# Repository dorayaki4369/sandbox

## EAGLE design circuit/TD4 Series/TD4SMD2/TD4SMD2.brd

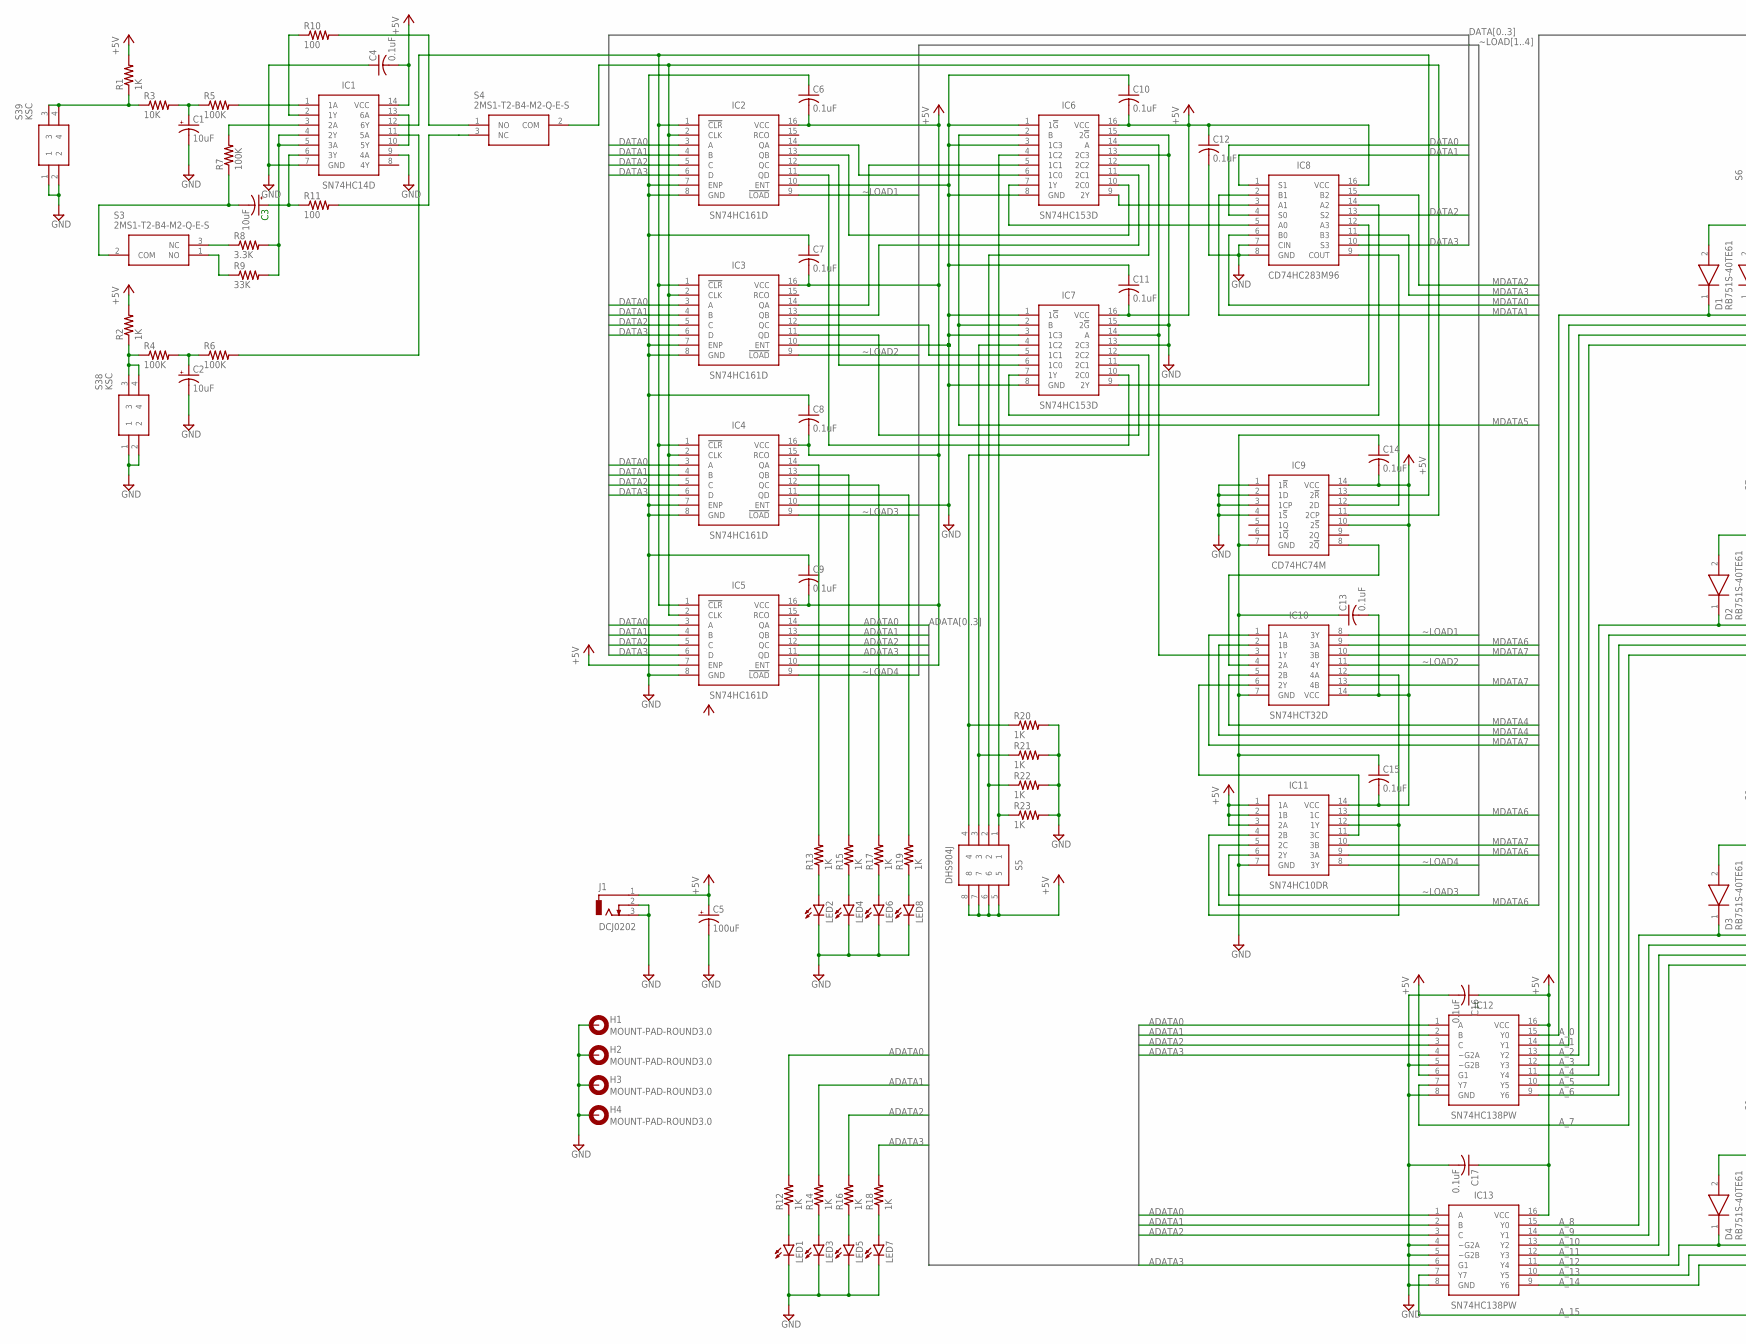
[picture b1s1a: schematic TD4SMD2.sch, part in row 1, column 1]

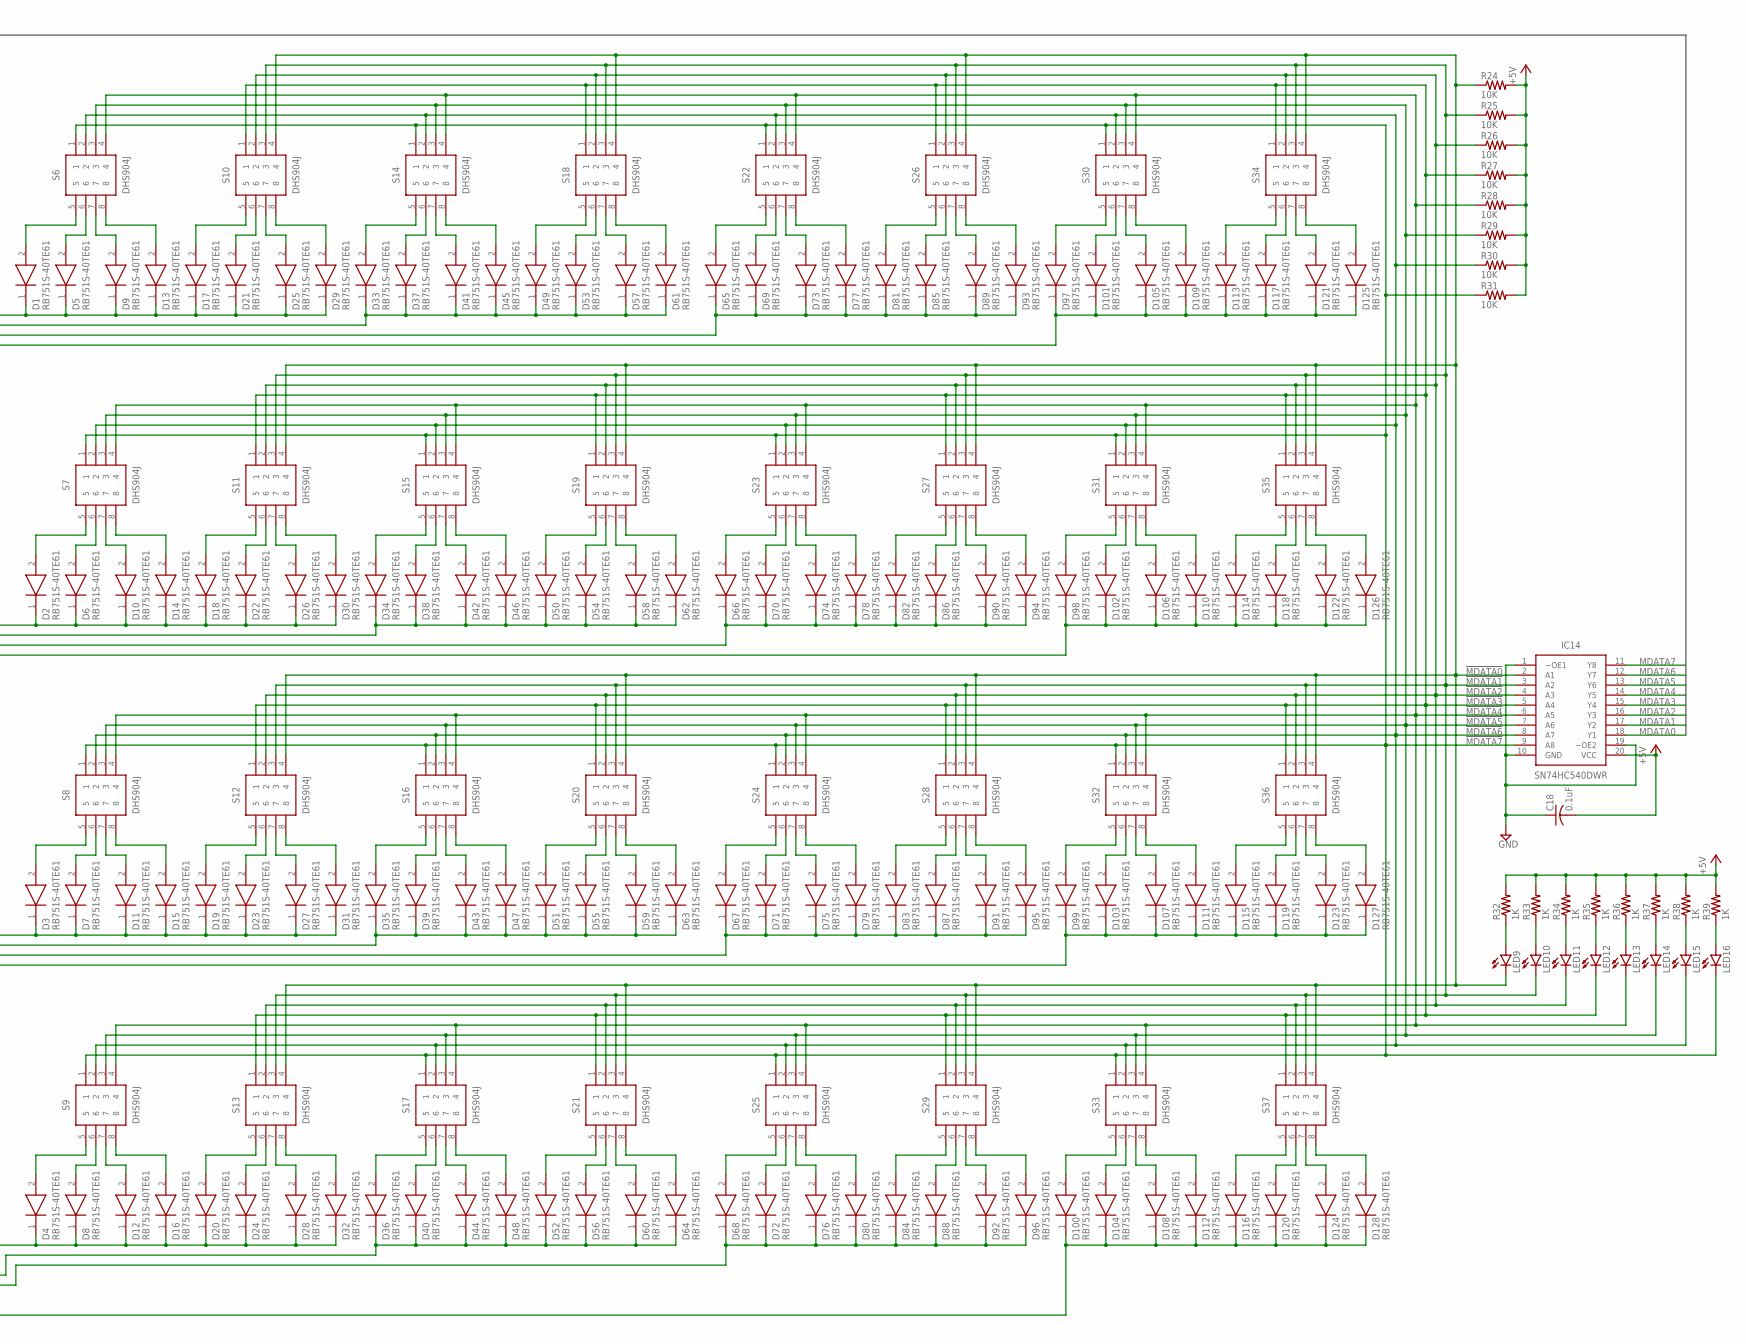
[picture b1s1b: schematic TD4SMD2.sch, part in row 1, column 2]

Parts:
C1, C2, C3: 10uF; 153CLV-0405
C4, C6, C7, C8, C9, C10, C11, C12, C13, C14, C15, C16, C17, C18: 0.1uF; C0603
C5: 100uF; 153CLV-1010
D1, D2, D3, D4, D5, D6, D7, D8, D9, D10, D11, D12, D13, D14, D15, D16, D17, D18, D19, D20, D21, D22, D23, D24, D25, D26, D27, D28, D29, D30, D31, D32, D33, D34, D35, D36, D37, D38, D39, D40, D41, D42, D43, D44, D45, D46, D47, D48, D49, D50, D51, D52, D53, D54, D55, D56, D57, D58, D59, D60, D61, D62, D63, D64, D65, D66, D67, D68, D69, D70, D71, D72, D73, D74, D75, D76, D77, D78, D79, D80, D81, D82, D83, D84, D85, D86, D87, D88, D89, D90, D91, D92, D93, D94, D95, D96, D97, D98, D99, D100, D101, D102, D103, D104, D105, D106, D107, D108, D109, D110, D111, D112, D113, D114, D115, D116, D117, D118, D119, D120, D121, D122, D123, D124, D125, D126, D127, D128: RB751S-40TE61; SODFL1608X70N
H1, H2, H3, H4: MOUNT-PAD-ROUND3.0; 3,0-PAD
IC1: SN74HC14D; SOIC127P600X175-14N
IC2, IC3, IC4, IC5: SN74HC161D; SOIC127P600X175-16N
IC6, IC7: SN74HC153D; SOIC127P600X175-16N
IC8: CD74HC283M96; SOIC127P600X175-16N
IC9: CD74HC74M; SOIC127P600X175-14N
IC10: SN74HCT32D; SOIC127P600X175-14N
IC11: SN74HC10DR; SOIC127P600X175-14N
IC12, IC13: SN74HC138PW; SOP65P640X120-16N
IC14: SN74HC540DWR; SOIC127P1030X265-20N
J1: DCJ0202
LED1, LED2, LED3, LED4, LED5, LED6, LED7, LED8, LED9, LED10, LED11, LED12, LED13, LED14, LED15, LED16: LEDCHIP-LED0603; CHIP-LED0603
R1, R2, R12, R13, R14, R15, R16, R17, R18, R19, R20, R21, R22, R23, R32, R33, R34, R35, R36, R37, R38, R39: 1K; R0603
R3, R24, R25, R26, R27, R28, R29, R30, R31: 10K; R0603
R4, R5, R6, R7: 100K; R0603
R8: 3.3K; R0603
R9: 33K; R0603
R10, R11: 100; R0603
S3, S4: 2MS1-T2-B4-M2-Q-E-S; 2MS1T2B4M2QES
S5, S6, S7, S8, S9, S10, S11, S12, S13, S14, S15, S16, S17, S18, S19, S20, S21, S22, S23, S24, S25, S26, S27, S28, S29, S30, S31, S32, S33, S34, S35, S36, S37: DHS904J
S38, S39: KSC

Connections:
!MDATA0: IC14.2 (A1), LED9.C, R24.1, S10.4, S11.4, S12.4, S13.4, S18.4, S19.4, S20.4, S21.4, S26.4, S27.4, S28.4, S29.4, S34.4, S35.4, S36.4, S37.4
!MDATA1: IC14.3 (A2), LED10.C, R25.1, S10.3, S11.3, S12.3, S13.3, S18.3, S19.3, S20.3, S21.3, S26.3, S27.3, S28.3, S29.3, S34.3, S35.3, S36.3, S37.3
!MDATA2: IC14.4 (A3), LED11.C, R26.1, S10.2, S11.2, S12.2, S13.2, S18.2, S19.2, S20.2, S21.2, S26.2, S27.2, S28.2, S29.2, S34.2, S35.2, S36.2, S37.2
!MDATA3: IC14.5 (A4), LED12.C, R27.1, S10.1, S11.1, S12.1, S13.1, S18.1, S19.1, S20.1, S21.1, S26.1, S27.1, S28.1, S29.1, S34.1, S35.1, S36.1, S37.1
!MDATA4: IC14.6 (A5), LED13.C, R28.1, S6.4, S7.4, S8.4, S9.4, S14.4, S15.4, S16.4, S17.4, S22.4, S23.4, S24.4, S25.4, S30.4, S31.4, S32.4, S33.4
!MDATA5: IC14.7 (A6), LED14.C, R29.1, S6.3, S7.3, S8.3, S9.3, S14.3, S15.3, S16.3, S17.3, S22.3, S23.3, S24.3, S25.3, S30.3, S31.3, S32.3, S33.3
!MDATA6: IC14.8 (A7), LED15.C, R30.1, S6.2, S7.2, S8.2, S9.2, S14.2, S15.2, S16.2, S17.2, S22.2, S23.2, S24.2, S25.2, S30.2, S31.2, S32.2, S33.2
!MDATA7: IC14.9 (A8), LED16.C, R31.1, S6.1, S7.1, S8.1, S9.1, S14.1, S15.1, S16.1, S17.1, S22.1, S23.1, S24.1, S25.1, S30.1, S31.1, S32.1, S33.1
+5V: C4.2, C5.+, C6.2, C7.2, C8.2, C9.2, C10.2, C11.2, C12.1, C13.2, C14.2, C15.2, C16.1, C17.1, C18.2, IC1.14 (VCC), IC2.16 (VCC), IC3.16 (VCC), IC4.16 (VCC), IC5.7 (ENP), IC5.10 (ENT), IC5.16 (VCC), IC6.16 (VCC), IC7.16 (VCC), IC8.16 (VCC), IC9.10 (2!S), IC9.14 (VCC), IC10.14 (VCC), IC11.1 (1A), IC11.2 (1B), IC11.3 (2A), IC11.14 (VCC), IC12.6 (G1), IC12.16 (VCC), IC13.16 (VCC), IC14.20 (VCC), J1.1, R1.2, R2.2, R24.2, R25.2, R26.2, R27.2, R28.2, R29.2, R30.2, R31.2, R32.2, R33.2, R34.2, R35.2, R36.2, R37.2, R38.2, R39.2, S5.5, S5.6, S5.7, S5.8
ADATA0: IC5.14 (QA), IC12.1 (A), IC13.1 (A), R12.2
ADATA1: IC5.13 (QB), IC12.2 (B), IC13.2 (B), R14.2
ADATA2: IC5.12 (QC), IC12.3 (C), IC13.3 (C), R16.2
ADATA3: IC5.11 (QD), IC12.4 (~G2A), IC13.6 (G1), R18.2
A_0: D1.1 (K), D5.1 (K), D9.1 (K), D13.1 (K), D17.1 (K), D21.1 (K), D25.1 (K), D29.1 (K), IC12.15 (Y0)
A_1: D33.1 (K), D37.1 (K), D41.1 (K), D45.1 (K), D49.1 (K), D53.1 (K), D57.1 (K), D61.1 (K), IC12.14 (Y1)
A_2: D65.1 (K), D69.1 (K), D73.1 (K), D77.1 (K), D81.1 (K), D85.1 (K), D89.1 (K), D93.1 (K), IC12.13 (Y2)
A_3: D97.1 (K), D101.1 (K), D105.1 (K), D109.1 (K), D113.1 (K), D117.1 (K), D121.1 (K), D125.1 (K), IC12.12 (Y3)
A_4: D2.1 (K), D6.1 (K), D10.1 (K), D14.1 (K), D18.1 (K), D22.1 (K), D26.1 (K), D30.1 (K), IC12.11 (Y4)
A_5: D34.1 (K), D38.1 (K), D42.1 (K), D46.1 (K), D50.1 (K), D54.1 (K), D58.1 (K), D62.1 (K), IC12.10 (Y5)
A_6: D66.1 (K), D70.1 (K), D74.1 (K), D78.1 (K), D82.1 (K), D86.1 (K), D90.1 (K), D94.1 (K), IC12.9 (Y6)
A_7: D98.1 (K), D102.1 (K), D106.1 (K), D110.1 (K), D114.1 (K), D118.1 (K), D122.1 (K), D126.1 (K), IC12.7 (Y7)
A_8: D3.1 (K), D7.1 (K), D11.1 (K), D15.1 (K), D19.1 (K), D23.1 (K), D27.1 (K), D31.1 (K), IC13.15 (Y0)
A_9: D35.1 (K), D39.1 (K), D43.1 (K), D47.1 (K), D51.1 (K), D55.1 (K), D59.1 (K), D63.1 (K), IC13.14 (Y1)
A_10: D67.1 (K), D71.1 (K), D75.1 (K), D79.1 (K), D83.1 (K), D87.1 (K), D91.1 (K), D95.1 (K), IC13.13 (Y2)
A_11: D99.1 (K), D103.1 (K), D107.1 (K), D111.1 (K), D115.1 (K), D119.1 (K), D123.1 (K), D127.1 (K), IC13.12 (Y3)
A_12: D4.1 (K), D8.1 (K), D12.1 (K), D16.1 (K), D20.1 (K), D24.1 (K), D28.1 (K), D32.1 (K), IC13.11 (Y4)
A_13: D36.1 (K), D40.1 (K), D44.1 (K), D48.1 (K), D52.1 (K), D56.1 (K), D60.1 (K), D64.1 (K), IC13.10 (Y5)
A_14: D68.1 (K), D72.1 (K), D76.1 (K), D80.1 (K), D84.1 (K), D88.1 (K), D92.1 (K), D96.1 (K), IC13.9 (Y6)
A_15: D100.1 (K), D104.1 (K), D108.1 (K), D112.1 (K), D116.1 (K), D120.1 (K), D124.1 (K), D128.1 (K), IC13.7 (Y7)
DATA0: IC2.3 (A), IC3.3 (A), IC4.3 (A), IC5.3 (A), IC8.4 (S0)
DATA1: IC2.4 (B), IC3.4 (B), IC4.4 (B), IC5.4 (B), IC8.1 (S1)
DATA2: IC2.5 (C), IC3.5 (C), IC4.5 (C), IC5.5 (C), IC8.13 (S2)
DATA3: IC2.6 (D), IC3.6 (D), IC4.6 (D), IC5.6 (D), IC8.10 (S3)
GND: C1.-, C2.-, C4.1, C5.-, C6.1, C7.1, C8.1, C9.1, C10.1, C11.1, C12.2, C13.1, C14.1, C15.1, C16.2, C17.2, C18.1, H1.B3,0, H2.B3,0, H3.B3,0, H4.B3,0, IC1.7 (GND), IC1.9 (4A), IC2.7 (ENP), IC2.8 (GND), IC2.10 (ENT), IC3.7 (ENP), IC3.8 (GND), IC3.10 (ENT), IC4.7 (ENP), IC4.8 (GND), IC4.10 (ENT), IC5.8 (GND), IC6.1 (1!G), IC6.3 (1C3), IC6.8 (GND), IC6.13 (2C3), IC6.15 (2!G), IC7.1 (1!G), IC7.3 (1C3), IC7.8 (GND), IC7.13 (2C3), IC7.15 (2!G), IC8.7 (CIN), IC8.8 (GND), IC9.1 (1!R), IC9.2 (1D), IC9.3 (1CP), IC9.4 (1!S), IC9.7 (GND), IC10.7 (GND), IC11.7 (GND), IC12.5 (~G2B), IC12.8 (GND), IC13.4 (~G2A), IC13.5 (~G2B), IC13.8 (GND), IC14.1 (~OE1), IC14.10 (GND), IC14.19 (~OE2), J1.2, J1.3, LED1.C, LED2.C, LED3.C, LED4.C, LED5.C, LED6.C, LED7.C, LED8.C, R20.2, R21.2, R22.2, R23.2, S38.1, S38.2, S39.1, S39.2
MDATA0: IC8.6 (B0), IC14.18 (Y1)
MDATA1: IC8.2 (B1), IC14.17 (Y2)
MDATA2: IC8.15 (B2), IC14.16 (Y3)
MDATA3: IC8.11 (B3), IC14.15 (Y4)
MDATA4: IC10.2 (1B), IC10.5 (2B), IC14.14 (Y5)
MDATA5: IC6.2 (B), IC7.2 (B), IC14.13 (Y6)
MDATA6: IC10.9 (3A), IC11.5 (2C), IC11.9 (3A), IC11.13 (1C), IC14.12 (Y7)
MDATA7: IC10.1 (1A), IC10.10 (3B), IC10.13 (4B), IC11.10 (3B), IC14.11 (Y8)
unnamed: IC2.14 (QA), IC6.6 (1C0)
unnamed: IC2.13 (QB), IC6.10 (2C0)
unnamed: IC2.12 (QC), IC7.6 (1C0)
unnamed: IC7.7 (1Y), IC8.14 (A2)
unnamed: IC6.4 (1C2), R23.1, S5.1
unnamed: IC6.12 (2C2), R22.1, S5.2
unnamed: IC7.4 (1C2), R21.1, S5.3
unnamed: IC7.12 (2C2), R20.1, S5.4
unnamed: R1.1, R3.1, S39.3, S39.4
unnamed: IC3.14 (QA), IC6.5 (1C1)
unnamed: IC3.13 (QB), IC6.11 (2C1)
unnamed: IC3.11 (QD), IC7.11 (2C1)
unnamed: IC3.12 (QC), IC7.5 (1C1)
unnamed: IC4.14 (QA), R13.2
unnamed: IC4.13 (QB), R15.2
unnamed: IC4.12 (QC), R17.2
unnamed: IC4.11 (QD), R19.2
unnamed: LED2.A, R13.1
unnamed: LED4.A, R15.1
unnamed: LED6.A, R17.1
unnamed: LED8.A, R19.1
unnamed: IC2.11 (QD), IC7.10 (2C0)
unnamed: IC6.7 (1Y), IC8.5 (A0)
unnamed: IC1.12 (6Y), IC2.1 (!CLR), IC3.1 (!CLR), IC4.1 (!CLR), IC5.1 (!CLR), IC9.13 (2!R)
unnamed: IC2.2 (CLK), IC3.2 (CLK), IC4.2 (CLK), IC5.2 (CLK), IC9.11 (2CP), S4.2 (COM)
unnamed: IC6.9 (2Y), IC8.3 (A1)
unnamed: IC10.12 (4A), IC11.4 (2B), IC11.12 (1Y)
unnamed: IC7.9 (2Y), IC8.12 (A3)
unnamed: IC6.14 (A), IC7.14 (A), IC10.3 (1Y)
unnamed: LED9.A, R32.1
unnamed: IC9.8 (2!Q), IC10.4 (2A)
unnamed: IC10.6 (2Y), IC11.11 (3C)
unnamed: IC8.9 (COUT), IC9.12 (2D)
unnamed: D125.2 (A), S34.8
unnamed: D121.2 (A), S34.7
unnamed: IC1.2 (1Y), R10.1
unnamed: R10.2, S4.1 (NO)
unnamed: C1.+, R3.2, R5.1
unnamed: IC1.1 (1A), R5.2
unnamed: R11.2, S4.3 (NC)
unnamed: C3.+, IC1.6 (3Y), R11.1
unnamed: C3.-, R7.1, S3.2 (COM)
unnamed: IC1.3 (2A), R7.2
unnamed: IC1.4 (2Y), IC1.5 (3A), R8.2, R9.2
unnamed: R8.1, S3.3 (NC)
unnamed: R9.1, S3.1 (NO)
unnamed: IC1.10 (5Y), IC1.13 (6A)
unnamed: IC1.11 (5A), R6.2
unnamed: R2.1, R4.1, S38.3, S38.4
unnamed: C2.+, R4.2, R6.1
unnamed: D117.2 (A), S34.6
unnamed: D113.2 (A), S34.5
unnamed: D109.2 (A), S30.8
unnamed: D105.2 (A), S30.7
unnamed: D101.2 (A), S30.6
unnamed: D97.2 (A), S30.5
unnamed: D93.2 (A), S26.8
unnamed: D89.2 (A), S26.7
unnamed: D85.2 (A), S26.6
unnamed: D81.2 (A), S26.5
unnamed: D77.2 (A), S22.8
unnamed: D73.2 (A), S22.7
unnamed: D69.2 (A), S22.6
unnamed: D65.2 (A), S22.5
unnamed: D127.2 (A), S36.8
unnamed: D61.2 (A), S18.8
unnamed: D57.2 (A), S18.7
unnamed: D53.2 (A), S18.6
unnamed: D49.2 (A), S18.5
unnamed: D45.2 (A), S14.8
unnamed: D41.2 (A), S14.7
unnamed: D37.2 (A), S14.6
unnamed: D33.2 (A), S14.5
unnamed: D29.2 (A), S10.8
unnamed: D25.2 (A), S10.7
unnamed: D21.2 (A), S10.6
unnamed: D17.2 (A), S10.5
unnamed: D13.2 (A), S6.8
unnamed: D9.2 (A), S6.7
unnamed: D5.2 (A), S6.6
unnamed: D1.2 (A), S6.5
unnamed: D126.2 (A), S35.8
unnamed: D122.2 (A), S35.7
unnamed: D118.2 (A), S35.6
unnamed: D114.2 (A), S35.5
unnamed: D110.2 (A), S31.8
unnamed: D106.2 (A), S31.7
unnamed: D102.2 (A), S31.6
unnamed: D98.2 (A), S31.5
unnamed: D94.2 (A), S27.8
unnamed: D90.2 (A), S27.7
unnamed: D86.2 (A), S27.6
unnamed: D82.2 (A), S27.5
unnamed: D78.2 (A), S23.8
unnamed: D74.2 (A), S23.7
unnamed: D70.2 (A), S23.6
unnamed: D66.2 (A), S23.5
unnamed: D62.2 (A), S19.8
unnamed: D58.2 (A), S19.7
unnamed: D54.2 (A), S19.6
unnamed: D50.2 (A), S19.5
unnamed: D46.2 (A), S15.8
unnamed: D42.2 (A), S15.7
unnamed: D38.2 (A), S15.6
unnamed: D34.2 (A), S15.5
unnamed: D30.2 (A), S11.8
unnamed: D26.2 (A), S11.7
unnamed: D22.2 (A), S11.6
unnamed: D18.2 (A), S11.5
unnamed: D14.2 (A), S7.8
unnamed: D10.2 (A), S7.7
unnamed: D6.2 (A), S7.6
unnamed: D2.2 (A), S7.5
unnamed: D123.2 (A), S36.7
unnamed: D119.2 (A), S36.6
unnamed: D115.2 (A), S36.5
unnamed: D111.2 (A), S32.8
unnamed: D107.2 (A), S32.7
unnamed: D103.2 (A), S32.6
unnamed: D99.2 (A), S32.5
unnamed: D95.2 (A), S28.8
unnamed: D91.2 (A), S28.7
unnamed: D87.2 (A), S28.6
unnamed: D83.2 (A), S28.5
unnamed: D79.2 (A), S24.8
unnamed: D75.2 (A), S24.7
unnamed: D71.2 (A), S24.6
unnamed: D67.2 (A), S24.5
unnamed: D63.2 (A), S20.8
unnamed: D59.2 (A), S20.7
unnamed: D55.2 (A), S20.6
unnamed: D51.2 (A), S20.5
unnamed: D47.2 (A), S16.8
unnamed: D43.2 (A), S16.7
unnamed: D39.2 (A), S16.6
unnamed: D35.2 (A), S16.5
unnamed: D31.2 (A), S12.8
unnamed: D27.2 (A), S12.7
unnamed: D23.2 (A), S12.6
unnamed: D19.2 (A), S12.5
unnamed: D15.2 (A), S8.8
unnamed: D11.2 (A), S8.7
unnamed: D7.2 (A), S8.6
unnamed: D3.2 (A), S8.5
unnamed: D128.2 (A), S37.8
unnamed: D124.2 (A), S37.7
unnamed: D120.2 (A), S37.6
unnamed: D116.2 (A), S37.5
unnamed: D112.2 (A), S33.8
unnamed: D108.2 (A), S33.7
unnamed: D104.2 (A), S33.6
unnamed: D100.2 (A), S33.5
unnamed: D96.2 (A), S29.8
unnamed: D92.2 (A), S29.7
unnamed: D88.2 (A), S29.6
unnamed: D84.2 (A), S29.5
unnamed: D80.2 (A), S25.8
unnamed: D76.2 (A), S25.7
unnamed: D72.2 (A), S25.6
unnamed: D68.2 (A), S25.5
unnamed: D64.2 (A), S21.8
unnamed: D60.2 (A), S21.7
unnamed: D56.2 (A), S21.6
unnamed: D52.2 (A), S21.5
unnamed: D48.2 (A), S17.8
unnamed: D44.2 (A), S17.7
unnamed: D40.2 (A), S17.6
unnamed: D36.2 (A), S17.5
unnamed: D32.2 (A), S13.8
unnamed: D28.2 (A), S13.7
unnamed: D24.2 (A), S13.6
unnamed: D20.2 (A), S13.5
unnamed: D16.2 (A), S9.8
unnamed: D12.2 (A), S9.7
unnamed: D8.2 (A), S9.6
unnamed: D4.2 (A), S9.5
unnamed: LED10.A, R33.1
unnamed: LED12.A, R35.1
unnamed: LED11.A, R34.1
unnamed: LED1.A, R12.1
unnamed: LED3.A, R14.1
unnamed: LED5.A, R16.1
unnamed: LED7.A, R18.1
unnamed: LED13.A, R36.1
unnamed: LED14.A, R37.1
unnamed: LED15.A, R38.1
unnamed: LED16.A, R39.1
~LOAD1: IC2.9 (!LOAD), IC10.8 (3Y)
~LOAD2: IC3.9 (!LOAD), IC10.11 (4Y)
~LOAD3: IC4.9 (!LOAD), IC11.6 (2Y)
~LOAD4: IC5.9 (!LOAD), IC11.8 (3Y)

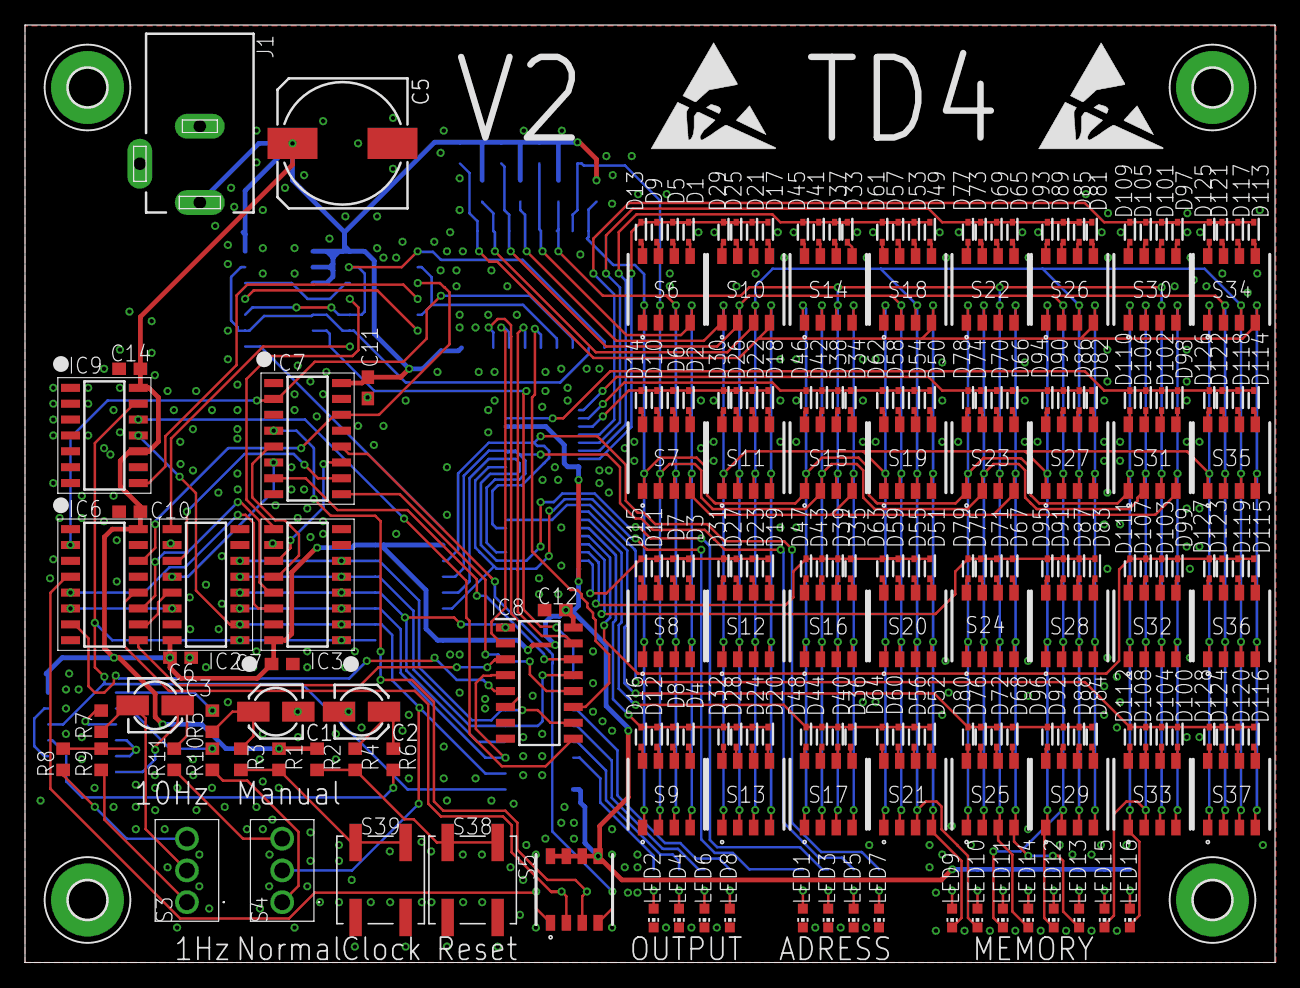
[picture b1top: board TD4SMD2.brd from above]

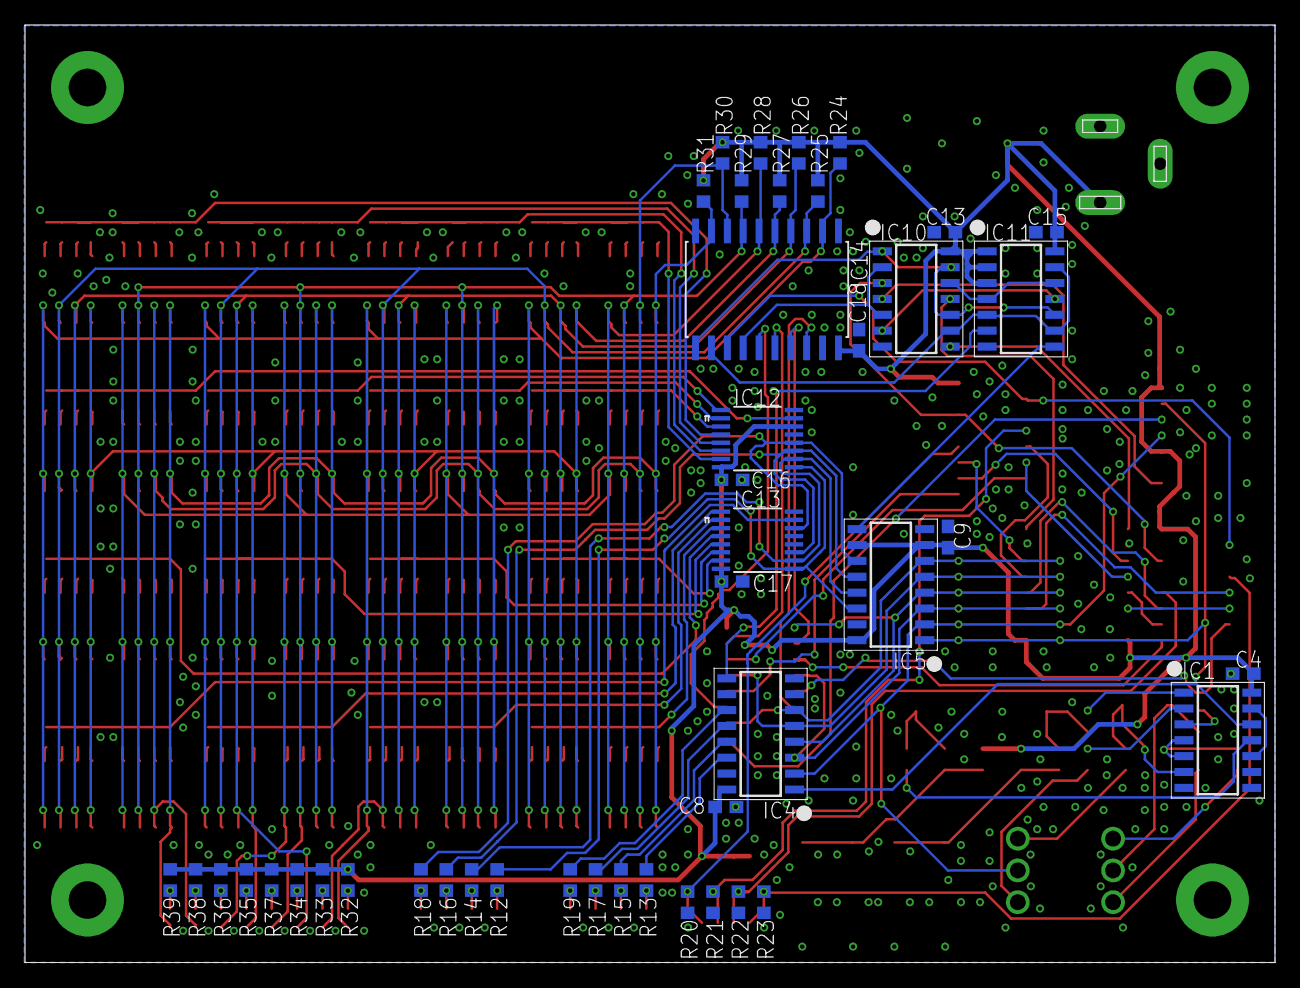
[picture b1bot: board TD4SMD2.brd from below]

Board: 2 copper layers, 100.0 x 75.0 mm, 259 parts (44 on the bottom side), 233 nets.

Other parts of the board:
U$1, U$2: ESD_10.00

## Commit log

2023-01-23 init
